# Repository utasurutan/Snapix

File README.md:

# Snapix

[Picture]

> **A dynamic digital ID with a built-in camera that turns live photos into retro 8-bit pixel art on screen!**

---

## Overview

**What is it about?**  
Snapix is a dynamic digital ID with a built-in camera that turns live photos into retro 8-bit pixel art—press a button to snap and display your pixel avatar alongside your ID profile.

**How to do i use it?**  
1. **Power On:** Turn on Snapix using the power switch
2. **Snap a Photo:** Press the shutter button to preview the live camera, then press again to capture your portrait.
3. **Display ID:** Snapix instantly converts the photo into 8-bit pixel art and displays it next to your ID profile.
4. **Edit:** You can change your display name, profile picture and also the color of the ID background!

**Why we made it**  
Event badges and IDs are usually static, disposable, and forgettable. We wanted to build something that's a wearable hardware that's playful, unique, and a form of self-expression!

---

## Demo & Final Build

### Demo Video
[Snapix Demo Video] -

### Final Product Gallery
[Snapix Final Product] -

---

## Design & Hardware Architecture

### Full 3D Assembly & Render
! -

### PCB Layout
! -

### Schematic
The electronic schematic is divided into four sheets, covering the main components and their connections.

**01. Power, Charging & Protection**

**02. ESP32-S3-WROOM-1**

**03. OV2640 Camera**

**04. TFT, microSD & Buttons**

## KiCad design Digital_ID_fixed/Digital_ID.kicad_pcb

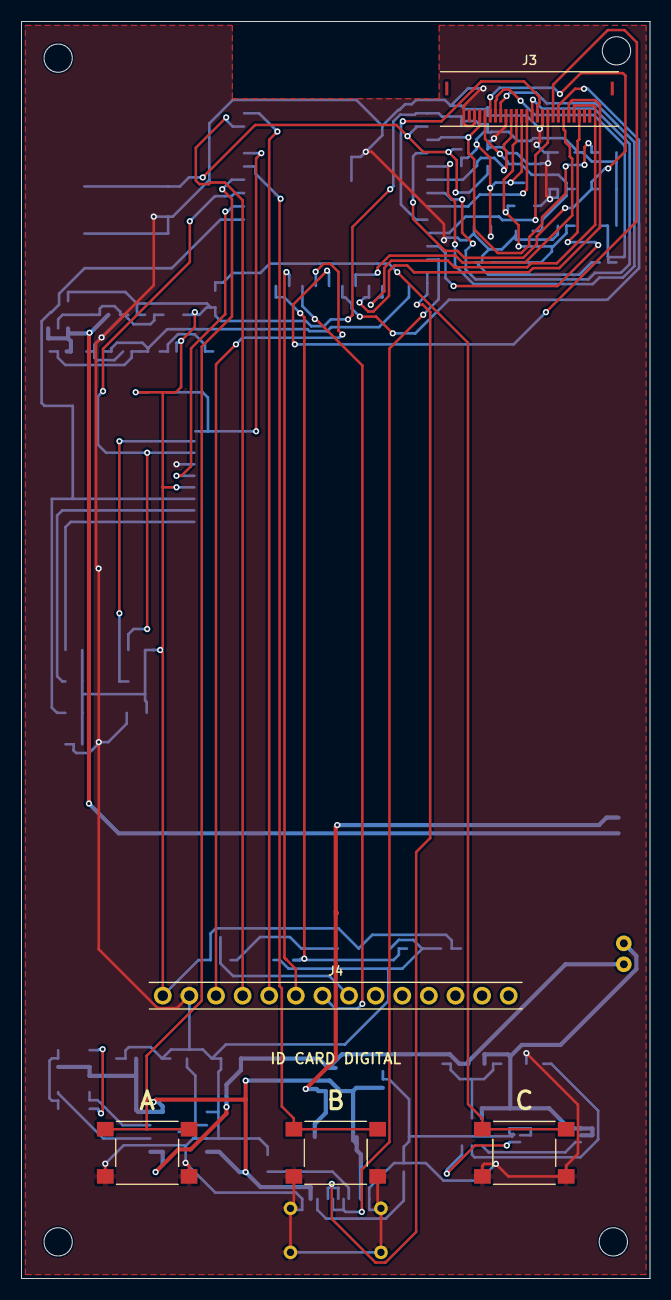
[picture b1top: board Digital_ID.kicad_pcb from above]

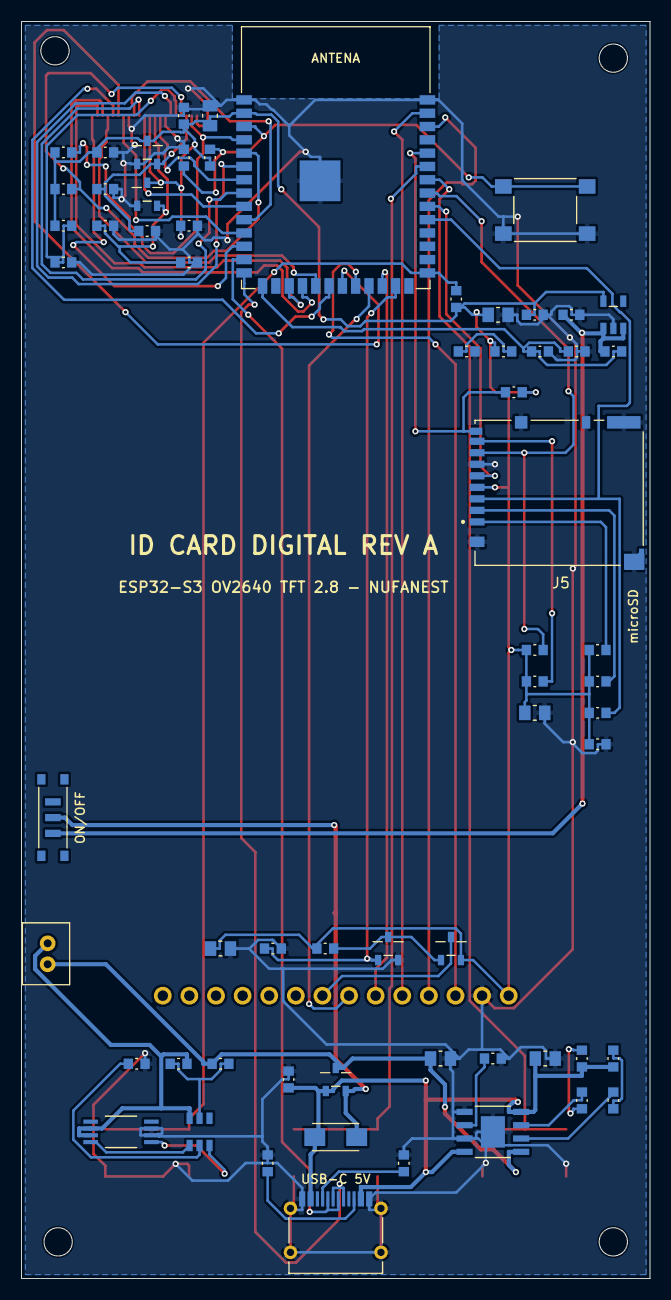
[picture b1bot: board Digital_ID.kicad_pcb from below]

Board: 2 copper layers, 60.0 x 120.0 mm, 72 parts (63 on the bottom side), 58 nets.

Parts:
C1, C2, C18, C19: 10uF; 0805
C3, C7, C10, C14, C15, C16, C17, C20: 100nF; 0603
C4, C5, C8, C11, C12, C13: 1uF; 0603
C6, C9: 22uF; 0805
D1: MERAH; LED0603
D2, D4: HIJAU; LED0603
D3: SS14; SMA
J1: USB-C 16P; USB-C-16P
J2: BATERAI LIPO 1S; JST-PH2
J3: OV2640 FPC 24P; FPC24-0.5
J4: TFT 2.8in ILI9341; HDR1X14
J5: DM3BT-DSF-PEJS; HRS_DM3BT-DSF-PEJS
Q1, Q3: AO3401; SOT23
Q4: 2N7002; SOT23
R1, R2: 5.1k; 0603
R3: 3.3k; 0603
R4, R5, R7: 1k; 0603
R6: 100R; 0603
R8, R10, R11, R18: 100k; 0603
R9: 2.2k; 0603
R12, R13, R14, R17, R19, R20, R21, R22, R23, R24: 10k; 0603
R15, R16: 4.7k; 0603
SW1: MSK-12C02; MSK12C02
SW2: TOMBOL A; TACT6X6
SW3: TOMBOL B; TACT6X6
SW4: TOMBOL C; TACT6X6
SW5: RESET; TACT6X6
U1: TP4056; SOP8-EP
U2: DW01A; SOT23-6
U3: FS8205A; TSSOP8
U4: TLV75733PDBV; SOT23-5
U5: ESP32-S3-WROOM-1-N16R8; ESP32-S3-WROOM-1
U6: XC6206P282MR; SOT23
U7: XC6206P122MR; SOT23
UNK_HOLE_0: dummyfp0
UNK_HOLE_1: dummyfp1
UNK_HOLE_2: dummyfp2
UNK_HOLE_3: dummyfp3

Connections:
1V2: C13.1, C17.1, J3.10, U7.2
2V8: C12.1, C16.1, J3.4, U6.2
3V3: C5.1, C6.1, C9.1, C10.1, C11.1, C15.1, C18.1, C19.1, C20.1, J3.11, J4.1, J5.4, Q3.2, R9.1, R12.1, R13.1, R14.1, R15.1, R16.1, R17.1, R19.1, R20.1, R21.1, R22.1, R23.1, R24.1, U4.5, U5.2, U6.3, U7.3
BAT+: C2.1, J2.1, Q1.3, R6.1, U1.5
BAT-: C3.2, J2.2, U2.6, U3.2, U3.3
BAT_SENSE: C7.1, R10.2, R11.1, U5.15
BL_G: Q3.1, Q4.3, R13.2
BTN_A: SW2.1, SW2.2, U5.34
BTN_B: SW3.1, SW3.2, U5.35
BTN_C: R14.2, SW4.1, SW4.2, U5.27
CAM_HREF: J3.9, U5.7
CAM_PCLK: J3.17, U5.21
CAM_RST: C14.1, J3.6, R17.2
CAM_SIOC: J3.5, R16.2, U5.5
CAM_SIOD: J3.3, R15.2, U5.4
CAM_VSYNC: J3.7, U5.6
CAM_XCLK: J3.13, U5.8
CAM_Y2: J3.19, U5.19
CAM_Y3: J3.21, U5.17
CAM_Y4: J3.22, U5.12
CAM_Y5: J3.20, U5.18
CAM_Y6: J3.18, U5.20
CAM_Y7: J3.16, U5.11
CAM_Y8: J3.14, U5.10
CAM_Y9: J3.12, U5.9
CC1: J1.A5, R1.1
CC2: J1.B5, R2.1
CHRG: D1.C, U1.7
CS: R7.1, U2.2
DW_VCC: C3.1, R6.2, U2.5
EN: C8.1, R12.2, SW5.1, SW5.2, U5.3
GND: C1.2, C2.2, C4.2, C5.2, C6.2, C7.2, C8.2, C9.2, C10.2, C11.2, C12.2, C13.2, C14.2, C15.2, C16.2, C17.2, C18.2, C19.2, C20.2, D4.C, J1.A1B12, J1.B12A1, J1.S1, J1.S2, J1.S3, J1.S4, J3.2, J3.8, J3.15, J4.2, J5.6, J5.S1, J5.S2, J5.S3, J5.S4, J5.SW-A, Q4.2, R1.2, R2.2, R3.2, R7.2, R8.2, R11.2, R18.2, SW2.3, SW2.4, SW3.3, SW3.4, SW4.3, SW4.4, SW5.3, SW5.4, U1.1, U1.3, U1.9, U3.6, U3.7, U4.2, U5.1, U5.40, U5.41, U6.1, U7.1
N_D1: D1.A, R4.2
N_D2: D2.A, R5.2
N_D4: D4.A, R9.2
OC: U2.3, U3.5
OD: U2.1, U3.4
PROG: R3.1, U1.2
SD_CARD_DETECT: J5.SW-B, R24.2, U5.36
SD_CLK: J5.5, U5.32
SD_CMD: J5.3, R21.2, U5.31
SD_D0: J5.7, R22.2, U5.33
SD_D1: J5.8, R23.2
SD_D2: J5.1, R19.2
SD_D3: J5.2, R20.2
STDBY: D2.C, U1.6
TFT_BL: Q4.1, R18.1, U5.25
TFT_CS: J4.3, U5.22
TFT_DC: J4.5, U5.39
TFT_LED: J4.8, Q3.3
TFT_MOSI: J4.6, U5.24
TFT_RST: J4.4, U5.38
TFT_SCK: J4.7, U5.23
USB_DN: J1.A7, J1.B7, U5.13
USB_DP: J1.A6, J1.B6, U5.14
VBUS: C1.1, D3.A, J1.A4B9, J1.B4A9, Q1.1, R4.1, R5.1, R8.1, U1.4, U1.8
VSW: C4.1, R10.1, SW1.1, U4.1, U4.3
VSYS: D3.C, Q1.2, SW1.2
